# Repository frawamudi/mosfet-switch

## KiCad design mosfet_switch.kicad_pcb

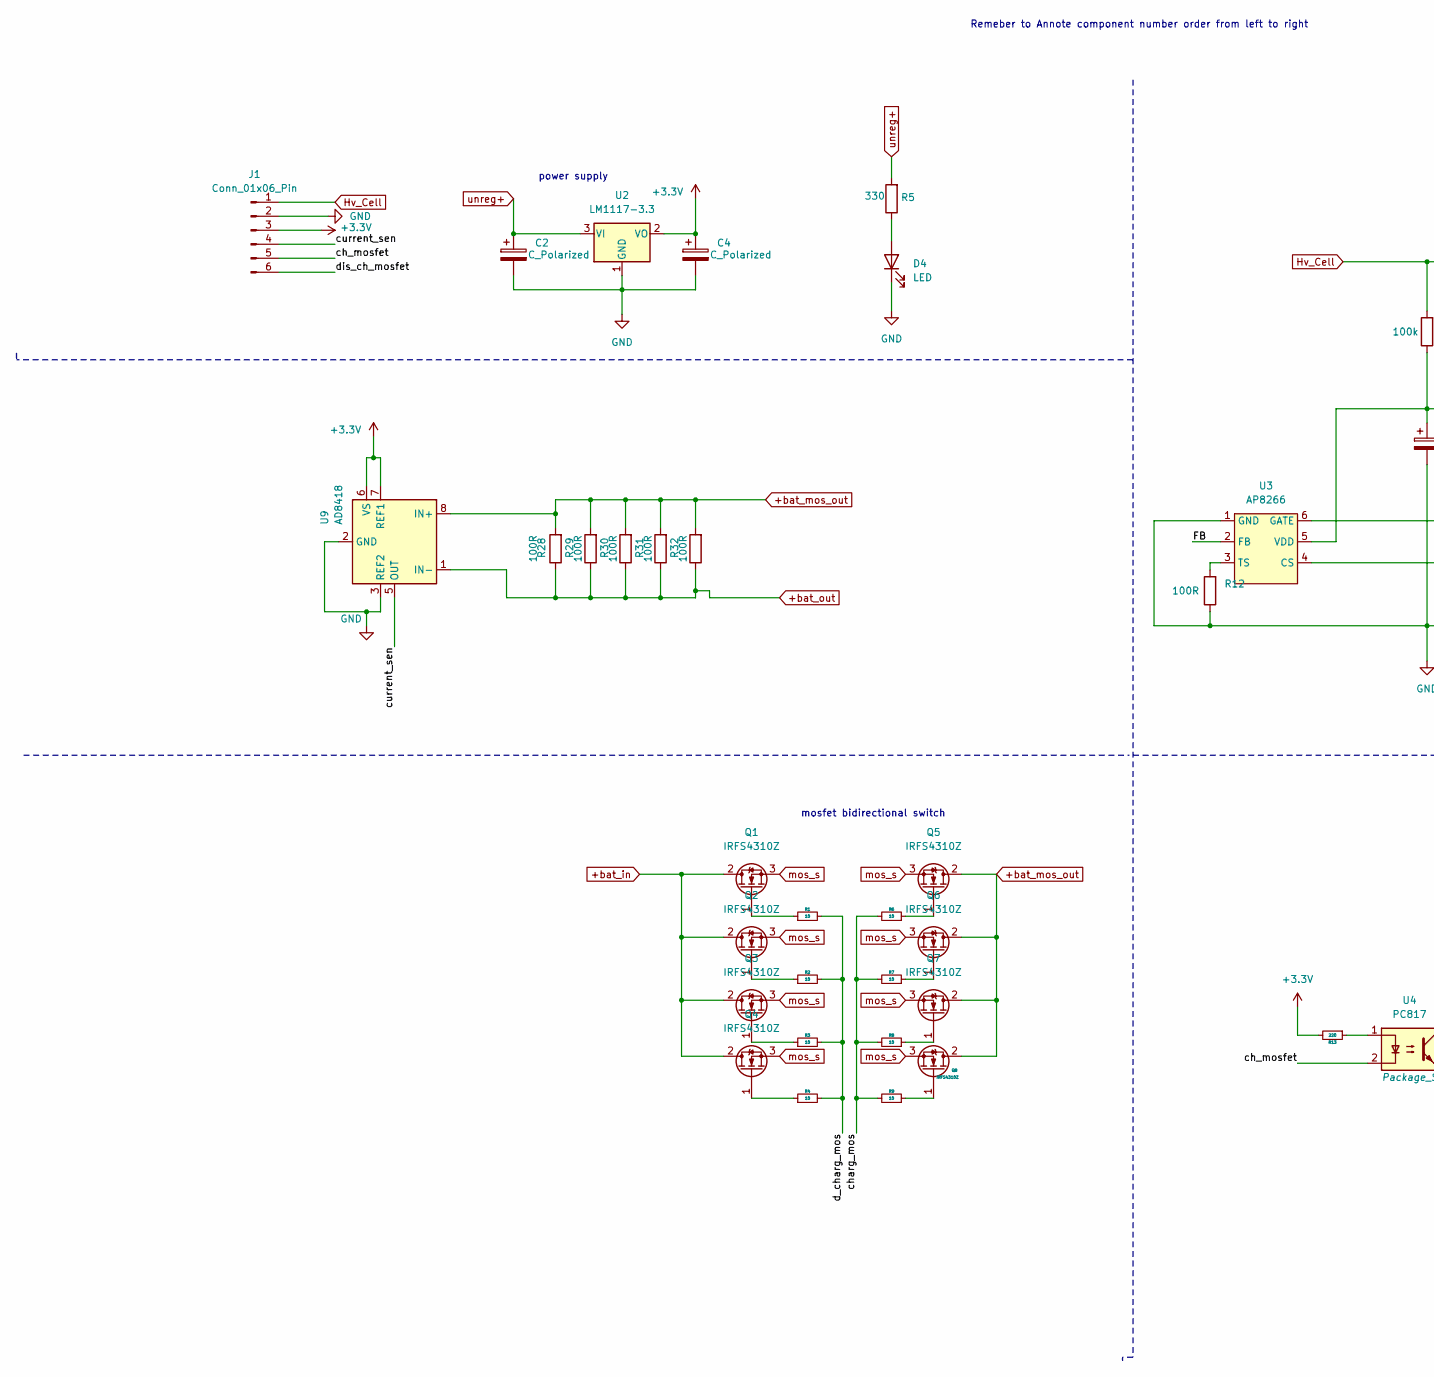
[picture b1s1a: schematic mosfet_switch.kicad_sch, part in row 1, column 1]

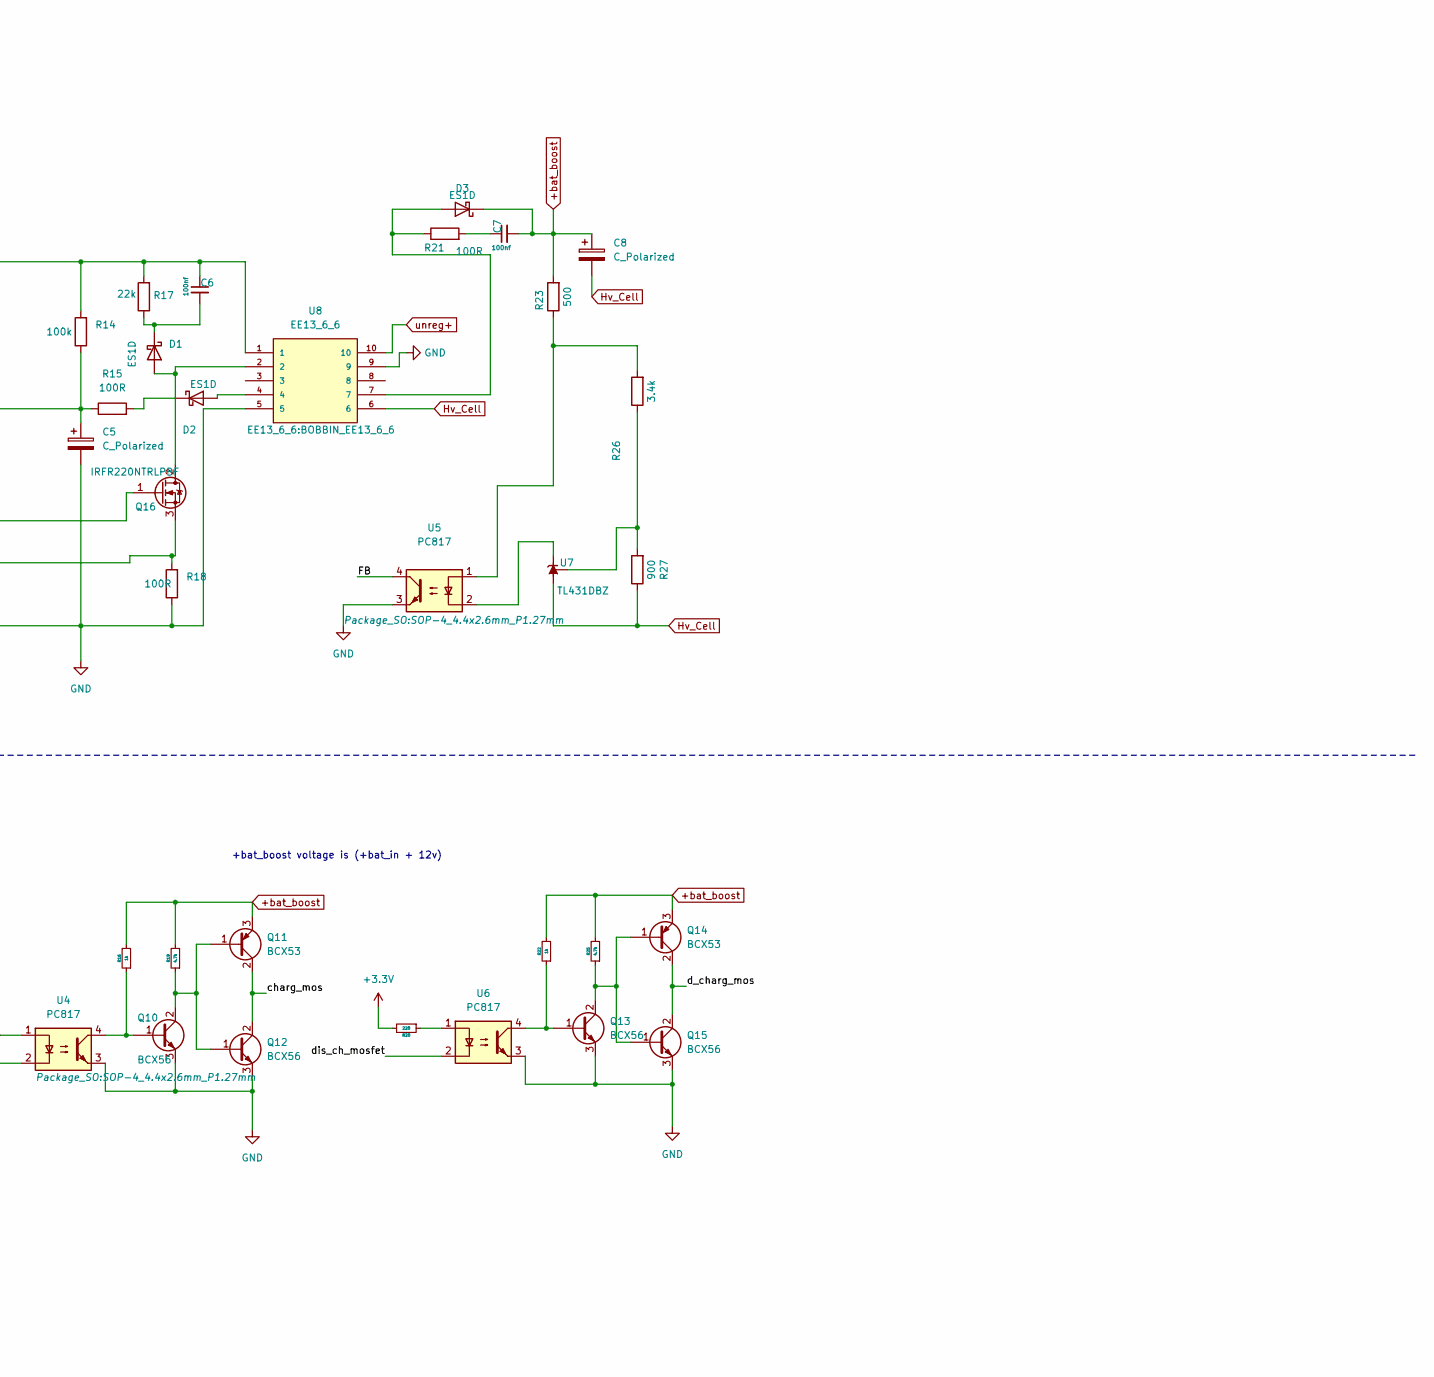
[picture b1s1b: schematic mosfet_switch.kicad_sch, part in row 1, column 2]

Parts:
C2, C4, C5, C8: C_Polarized; CP_Elec_3x5.4
C6, C7: 100nf; C_0402_1005Metric
D1, D2, D3: ES1D; D_SMA
D4: LED; LED_0402_1005Metric
J1: Conn_01x06_Pin; PinSocket_1x06_P2.54mm_Vertical
Q1, Q2, Q3, Q4, Q5, Q6, Q7, Q8: IRFS4310Z; TO-263-2
Q10, Q12, Q13, Q15: BCX56; SOT-89-3
Q11, Q14: BCX53; SOT-89-3
Q16: IRFR220NTRLPBF; TO-252-2
R1, R2, R3, R4, R6, R7, R8, R9: 10; R_0402_1005Metric
R5: 330; R_0402_1005Metric
R12, R15, R18, R21: 100R; R_0402_1005Metric
R13, R20: 220; R_0402_1005Metric
R14: 100k; R_0402_1005Metric
R16, R22: 1k; R_0402_1005Metric
R17: 22k; R_0402_1005Metric
R19, R25: 4.7k; R_0402_1005Metric
R23: 500; R_0402_1005Metric
R26: 3.4k; R_0402_1005Metric
R27: 900; R_0402_1005Metric
R28, R29, R30, R31, R32: 100R; R_2512_6332Metric_Pad1.40x3.35mm_HandSolder
U2: LM1117-3.3; SOT-223
U3: AP8266; SOT-23-6_Handsoldering
U4, U5, U6: PC817; SOP-4_4.4x2.6mm_P1.27mm
U7: TL431DBZ; SOT-23
U8: EE13_6_6; BOBBIN_EE13_6_6; PARTREV 11/19
U9: AD8418; SOIC-8-1EP_3.9x4.9mm_P1.27mm_EP2.29x3mm

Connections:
+3.3V: C4.1, J1.3, R13.2, R20.2, U2.2 (VO), U9.6 (VS), U9.7 (REF1)
+bat_boost: C7.2, C8.1, D3.1 (K), Q11.3 (E), Q14.3 (E), R16.2, R19.2, R22.2, R23.2, R25.2
+bat_in: Q1.2 (D), Q2.2 (D), Q3.2 (D), Q4.2 (D)
+bat_mos_out: Q5.2 (D), Q6.2 (D), Q7.2 (D), Q8.2 (D), R28.2, R29.2, R30.2, R31.2, R32.2, U9.8 (IN+)
+bat_out: R28.1, R29.1, R30.1, R31.1, R32.1, U9.1 (IN-)
/FB: U3.2 (FB), U5.4
/ch_mosfet: J1.5, U4.2
/charg_mos: Q11.2 (C), Q12.2 (C), R6.2, R7.2, R8.2, R9.2
/current_sen: J1.4, U9.5 (OUT)
/d_charg_mos: Q14.2 (C), Q15.2 (C), R1.2, R2.2, R3.2, R4.2
/dis_ch_mosfet: J1.6, U6.2
GND: C2.2, C4.2, C5.2, D4.1 (K), J1.2, Q10.3 (E), Q12.3 (E), Q13.3 (E), Q15.3 (E), R12.1, R18.1, U2.1 (GND), U3.1 (GND), U4.3, U5.3, U6.3, U8.5, U8.9, U9.2 (GND), U9.3 (REF2)
Hv_Cell: C6.1, C8.2, J1.1, R14.2, R17.2, R27.1, U7.3 (A), U8.1, U8.6
unnamed: C7.1, R21.2
unnamed: D1.2 (A), Q16.2 (D), U8.2
unnamed: C6.2, D1.1 (K), R17.1
unnamed: D2.2 (A), U8.4
unnamed: D2.1 (K), R15.2
unnamed: D3.2 (A), R21.1, U8.7
unnamed: D4.2 (A), R5.1
unnamed: Q1.1 (G), R1.1
unnamed: Q2.1 (G), R2.1
unnamed: Q3.1 (G), R3.1
unnamed: Q4.1 (G), R4.1
unnamed: Q5.1 (G), R6.1
unnamed: Q6.1 (G), R7.1
unnamed: Q7.1 (G), R8.1
unnamed: Q8.1 (G), R9.1
unnamed: Q10.1 (B), R16.1, U4.4
unnamed: Q10.2 (C), Q11.1 (B), Q12.1 (B), R19.1
unnamed: Q13.1 (B), R22.1, U6.4
unnamed: Q13.2 (C), Q14.1 (B), Q15.1 (B), R25.1
unnamed: Q16.1 (G), U3.6 (GATE)
unnamed: Q16.3 (S), R18.2, U3.4 (CS)
unnamed: R13.1, U4.1
unnamed: R20.1, U6.1
unnamed 36: R23.1, R26.2, U5.1; also elsewhere on the board
unnamed: R12.2, U3.3 (TS)
unnamed: C5.1, R14.1, R15.1, U3.5 (VDD)
unnamed 39: U5.2, U7.1 (K); also elsewhere on the board
unnamed: R26.1, R27.2, U7.2 (REF)
mos_s: Q1.3 (S), Q2.3 (S), Q3.3 (S), Q4.3 (S), Q5.3 (S), Q6.3 (S), Q7.3 (S), Q8.3 (S)
unreg+: C2.1, R5.2, U2.3 (VI), U8.10

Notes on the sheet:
+bat_boost voltage is (+bat_in + 12v)
Remeber to Annote component number order from left to right
mosfet bidirectional switch
power supply

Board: 2 copper layers, 64 parts (0 on the bottom side), 43 nets, no tracks yet.

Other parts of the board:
R24: 100R; R_0402_1005Metric

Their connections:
unnamed 36: R24.2; also elsewhere on the board
unnamed 39: R24.1; also elsewhere on the board

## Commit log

2024-11-11 Repo Setup: Setting Repo for Mosfet Switch
    First upstream push with all required directory till date.
2024-11-29 [clean up] [setup] : include backup folder to .gitignore
2024-11-29 [clean up] [set up]: another attempt to add backup folder to .gitignore
2024-11-30 [TL431 Circuit] Pick component value
    Work on calculating isolated voltage feed back circuitry
    changed smps switch mosfet.
